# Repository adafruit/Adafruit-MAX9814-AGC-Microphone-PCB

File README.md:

# Adafruit MAX9814 AGC Microphone PCB
<a href="http://www.adafruit.com/products/1713"><br/>
Click here to purchase one from the Adafruit shop</a>

Add an ear to your project with this well-designed electret microphone amplifier with AGC. This fully assembled and tested board comes with a 20-20KHz electret microphone soldered on. For the amplification, we use the Maxim MAX9814, a specialty chip that is designed for amplifying electret microphones in situations where the loudness of the audio isn't predictable.

The chip at the heart of this amp is the MAX9814, and has a few options you can configure with the breakout. The default 'max gain' is 60dB, but can be set to 40dB or 50dB by jumpering the Gain pin to VCC or ground. You can also change the Attack/Release ratio, from the default 1:4000 to 1:2000 or 1:500. The ouput from the amp is about 2Vpp max on a 1.25V DC bias, so it can be easily used with any Analog/Digital converter that is up to 3.3V input. If you want to pipe it into a Line Input, just use a 1-100uF blocking capacitor in series (100uF sounds best).

PCB files for MAX9814 AGC Microphone. The format is EagleCAD schematic and board layout

- https://www.adafruit.com/product/1713

### License

Adafruit invests time and resources providing this open source design, please support Adafruit and open-source hardware by purchasing products from [Adafruit](https://www.adafruit.com)!

All text above must be included in any redistribution

Designed by Limor Fried/Ladyada for Adafruit Industries.
Creative Commons Attribution/Share-Alike, all text above must be included in any redistribution. 
See license.txt for additional information.

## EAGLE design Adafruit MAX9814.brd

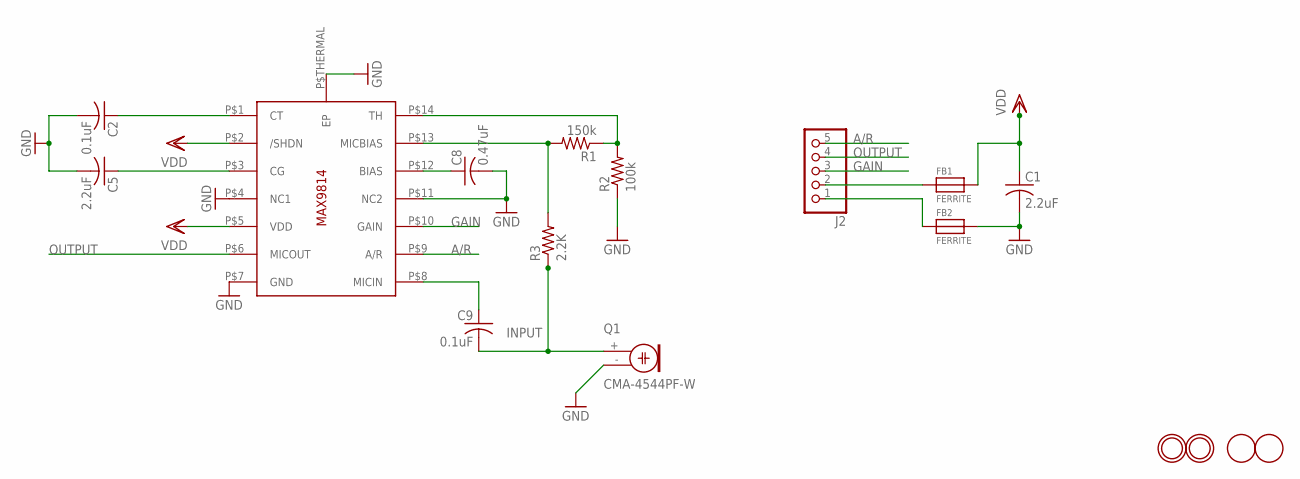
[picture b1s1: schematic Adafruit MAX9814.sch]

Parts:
C1, C5: 2.2uF; C0805K
C2, C9: 0.1uF; C0805K
C8: 0.47uF; C0805K
FB1, FB2: FERRITE; 0805
J2: HEADER-1X576MIL; 1X05_ROUND_76
Q1: CMA-4544PF-W; 9.7ELECTRET
R1: 150k; R0805
R2: 100k; R0805
R3: 2.2K; R0805
U$1: MAX9814TDFN14; TDFN14_3X3MM
U$2, U$3: FIDUCIAL; FIDUCIAL_1MM
U$4, U$5: MOUNTINGHOLE2.0; MOUNTINGHOLE_2.0_PLATED

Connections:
A/R: J2.5, U$1.P$9 (A/R)
GAIN: J2.3, U$1.P$10 (GAIN)
GND: C1.2, C2.2, C5.2, C8.2, FB2.2, Q1.- (1), R2.1, U$1.P$4 (NC1), U$1.P$7 (GND), U$1.P$11 (NC2), U$1.P$THERMAL (EP)
INPUT: C9.2, Q1.+ (2), R3.1
unnamed: FB1.1, J2.2
unnamed: FB2.1, J2.1
unnamed: C9.1, U$1.P$8 (MICIN)
unnamed: C8.1, U$1.P$12 (BIAS)
unnamed: C2.1, U$1.P$1 (CT)
unnamed: C5.1, U$1.P$3 (CG)
unnamed: R1.1, R2.2, U$1.P$14 (TH)
unnamed: R1.2, R3.2, U$1.P$13 (MICBIAS)
OUTPUT: J2.4, U$1.P$6 (MICOUT)
VDD: C1.1, FB1.2, U$1.P$2 (/SHDN), U$1.P$5 (VDD)

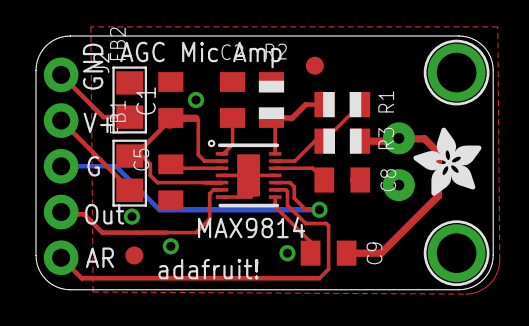
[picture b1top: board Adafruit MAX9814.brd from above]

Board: 2 copper layers, 25.4 x 14.1 mm, 18 parts (1 on the bottom side), 14 nets.

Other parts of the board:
U$6: ADAFRUIT_3.5MM

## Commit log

2015-05-04 init
